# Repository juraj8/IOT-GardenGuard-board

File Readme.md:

# Garden Guard

GardenGuard is an IOT type device created for collecting temperature data from multiple points in our garden. Main usecase for this data is to give alert for freezing weather in spring months, so user can take mitigation steps to prevent frost of the blooming fruit trees.

Freezing in spring months takes a lot of fruits from our garden. This is an attempt to hopefully get more fruits of our garden.  

## Features

- Uses multiple DS18x20 sensors to sample surrounding temperature.
- Solar and battery powered. Battery is charged wia solar panel, if battery is full, device only runs out of solar.  
- Battery voltage measurement.
- Battery should last over span of whole winter

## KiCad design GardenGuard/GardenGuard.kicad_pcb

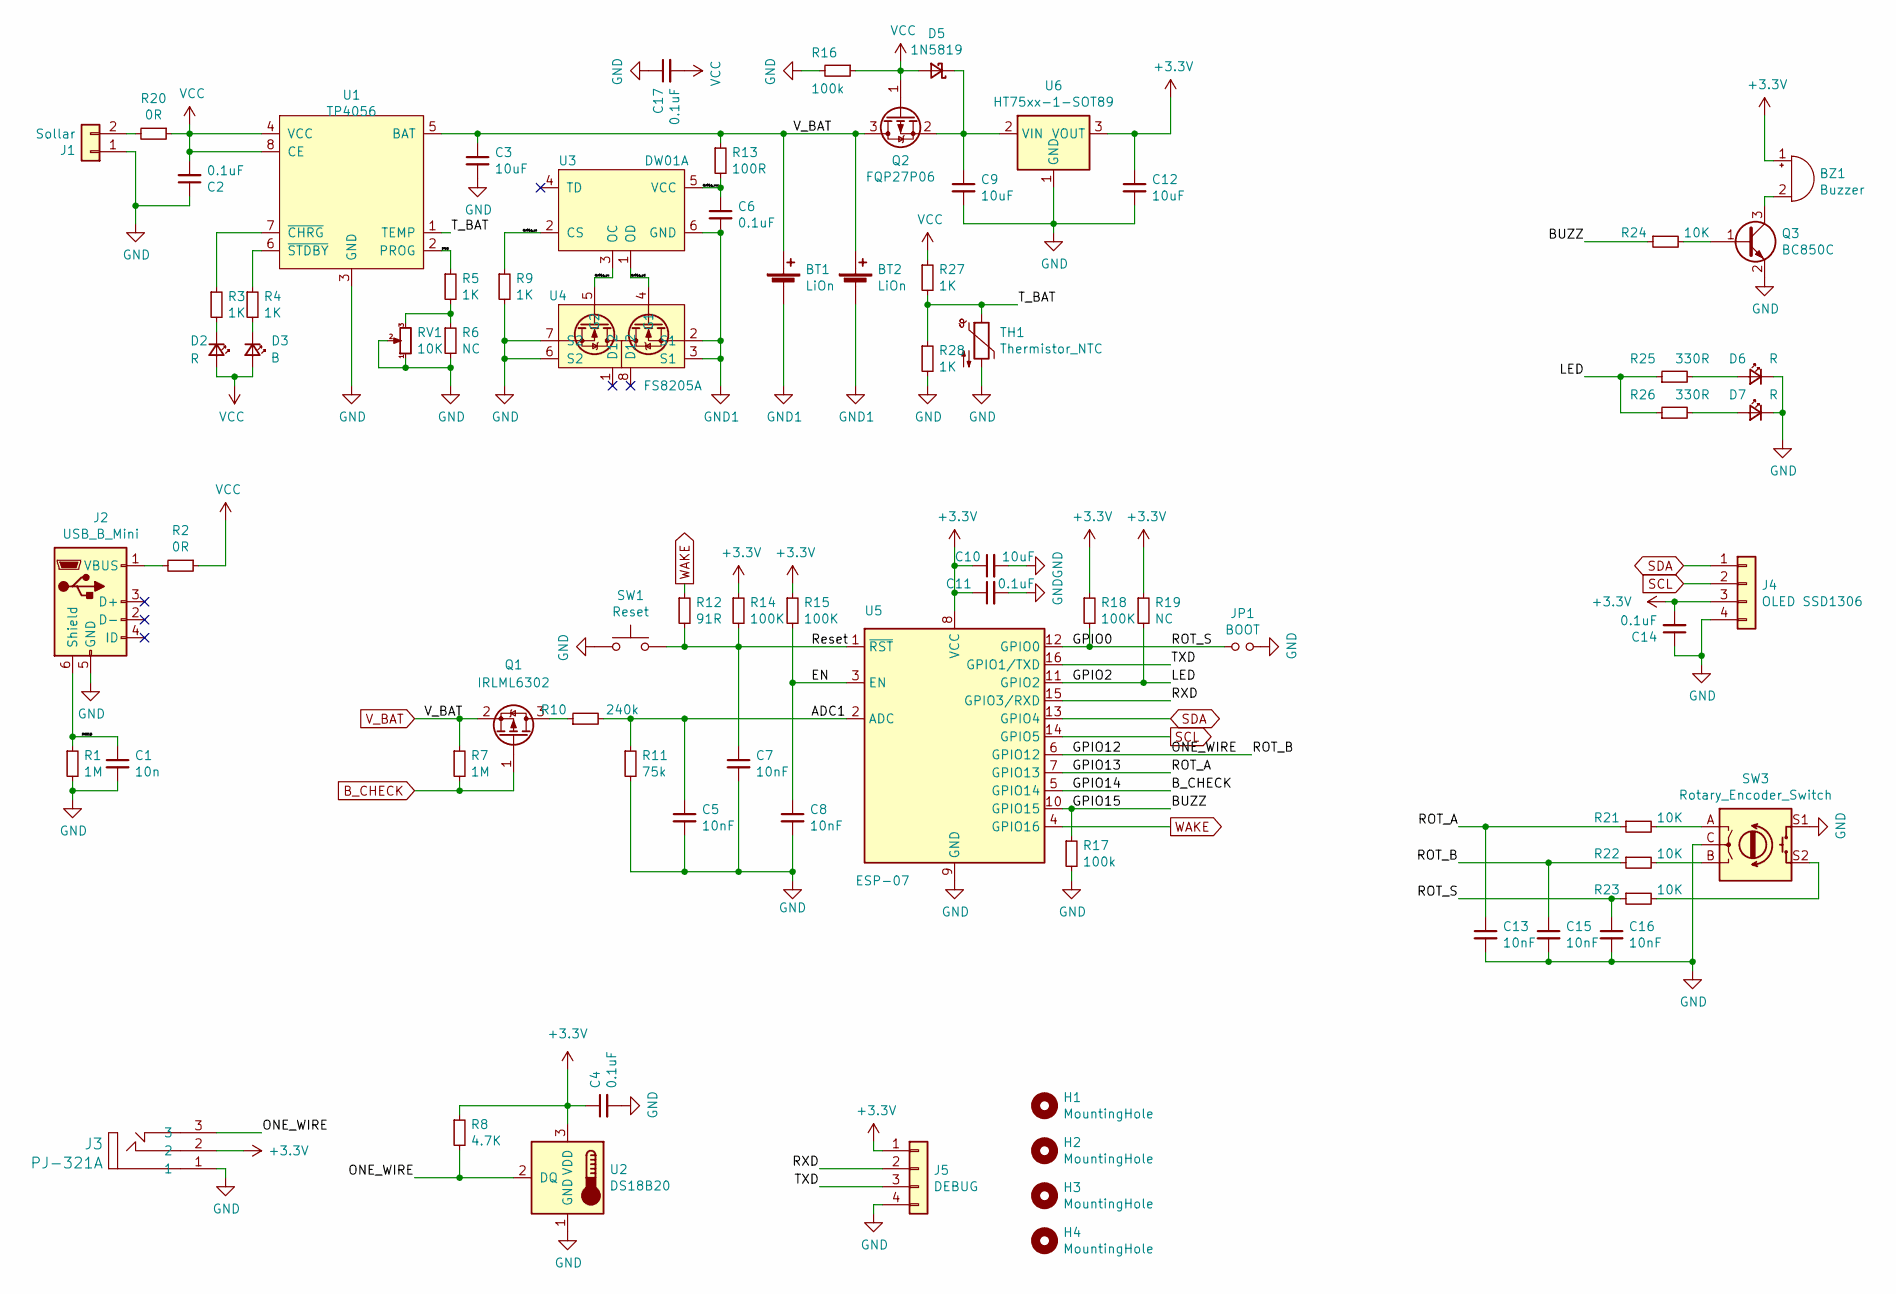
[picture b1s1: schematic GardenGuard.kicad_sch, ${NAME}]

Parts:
BT1, BT2: LiOn; BatteryHolder_Keystone_1042_1x18650
BZ1: Buzzer; Buzzer_12x9.5RM7.6
C1: 10n; C_0805_2012Metric_Pad1.18x1.45mm_HandSolder
C2, C17: 0.1uF; C_1206_3216Metric_Pad1.33x1.80mm_HandSolder
C3, C10: 10uF; C_1206_3216Metric_Pad1.33x1.80mm_HandSolder
C4, C6, C11, C14: 0.1uF; C_0805_2012Metric_Pad1.18x1.45mm_HandSolder
C5, C7, C8, C13, C15, C16: 10nF; C_0805_2012Metric_Pad1.18x1.45mm_HandSolder
C9, C12: 10uF; C_0805_2012Metric_Pad1.18x1.45mm_HandSolder
D2, D6, D7: R; LED_0805_2012Metric_Castellated
D3: B; LED_0805_2012Metric_Castellated
D5: 1N5819; D_SOD-123
H1, H2, H3, H4: MountingHole; MountingHole_3.2mm_M3_DIN965
J1: Sollar; ER-CON2.0-2P-SMD
J2: USB_B_Mini; USB_Micro-B_Amphenol_10118194_Horizontal
J3: PJ-321A
J4: OLED SSD1306; PinHeader_1x04_P2.54mm_Vertical
J5: DEBUG; PinHeader_1x04_P2.54mm_Vertical
JP1: BOOT; SolderJumper-2_P1.3mm_Open_RoundedPad1.0x1.5mm
Q1: IRLML6302; SOT-23_Handsoldering
Q2: FQP27P06; SOT-23_Handsoldering
Q3: BC850C; SOT-23_Handsoldering
R1, R7: 1M; R_0805_2012Metric_Pad1.20x1.40mm_HandSolder
R2, R20: 0R; R_0805_2012Metric_Pad1.20x1.40mm_HandSolder
R3, R4, R5, R9, R27, R28: 1K; R_0805_2012Metric_Pad1.20x1.40mm_HandSolder
R6, R19: NC; R_0805_2012Metric_Pad1.20x1.40mm_HandSolder
R8: 4.7K; R_0805_2012Metric_Pad1.20x1.40mm_HandSolder
R10: 240k; R_0805_2012Metric_Pad1.20x1.40mm_HandSolder
R11: 75k; R_0805_2012Metric_Pad1.20x1.40mm_HandSolder
R12: 91R; R_0805_2012Metric_Pad1.20x1.40mm_HandSolder
R13: 100R; R_0805_2012Metric_Pad1.20x1.40mm_HandSolder
R14, R15, R18: 100K; R_0805_2012Metric_Pad1.20x1.40mm_HandSolder
R16, R17: 100k; R_0805_2012Metric_Pad1.20x1.40mm_HandSolder
R21, R22, R23, R24: 10K; R_0805_2012Metric_Pad1.20x1.40mm_HandSolder
R25, R26: 330R; R_0805_2012Metric_Pad1.20x1.40mm_HandSolder
RV1: 10K; Potentiometer_Bourns_3224J_Horizontal
SW1: Reset; SW_SPST_B3U-3000P
SW3: Rotary_Encoder_Switch; RotaryEncoder_Alps_EC11E-Switch_Vertical_H20mm
TH1: Thermistor_NTC; R_Axial_DIN0204_L3.6mm_D1.6mm_P5.08mm_Horizontal
U1: TP4056; TP4056_SOP-8-PP
U2: DS18B20; TO-92_Inline
U3: DW01A; SOT-23-6
U4: FS8205A; TSSOP-8_4.4x3mm_P0.65mm
U5: ESP-07
U6: HT75xx-1-SOT89; SOT-89-3

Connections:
+3V3: BZ1.1 (-), C4.1, C10.1, C11.1, C12.1, C14.2, J3.2, J4.3, J5.1, R8.1, R14.1, R15.1, R18.1, R19.1, U2.3 (VDD), U5.8 (VCC), U6.3 (VOUT)
/ADC1: C5.1, R10.2, R11.1, U5.2 (ADC)
/BUZZ: R17.1, R24.1, U5.10 (GPIO15)
/EN: C8.1, R15.2, U5.3 (EN)
/GPIO0: C16.1, JP1.1, R18.2, R23.1, U5.12 (GPIO0)
/GPIO2: R19.2, R25.1, R26.1, U5.11 (GPIO2)
/GPIO12: C15.1, J3.3, R8.2, R22.1, U2.2 (DQ), U5.6 (GPIO12)
/GPIO13: C13.1, R21.1, U5.7 (GPIO13)
/RXD: J5.2, U5.15 (GPIO3/RXD)
/Reset: C7.1, R12.2, R14.2, SW1.2, U5.1 (~RST)
/SHIELD: C1.1, J2.6 (Shield), R1.1
/TXD: J5.3, U5.16 (GPIO1/TXD)
/T_BAT: R27.2, R28.1, TH1.1, U1.1 (TEMP)
/dw01a_cs: R9.1, U3.2 (CS)
/dw01a_oc: U3.3 (OC), U4.5 (G2)
/dw01a_od: U3.1 (OD), U4.4 (G1)
/dw01a_vcc: C6.1, R13.2, U3.5 (VCC)
/prog: R5.1, U1.2 (PROG)
B_CHECK: Q1.1 (G), R7.2, U5.5 (GPIO14)
GND: C1.2, C2.1, C3.2, C4.2, C5.2, C7.2, C8.2, C9.2, C10.2, C11.2, C12.2, C13.2, C14.1, C15.2, C16.2, C17.1, D6.1 (K), D7.1 (K), J1.1, J2.5 (GND), J3.1, J4.4, J5.4, JP1.2, Q3.2 (E), R1.2, R6.2, R9.2, R11.2, R16.2, R17.2, R28.2, RV1.1, RV1.2, SW1.1, SW3.C, SW3.S1, TH1.2, U1.3 (GND), U2.1 (GND), U4.6 (S2), U4.7 (S2), U5.9 (GND), U6.1 (GND)
GND1: BT1.2 (-), BT2.2 (-), C6.2, U3.6 (GND), U4.2 (S1), U4.3 (S1)
unnamed: BZ1.2 (+), Q3.3 (C)
unnamed: C9.1, D5.1 (K), Q2.2 (S), U6.2 (VIN)
unnamed: D2.1 (K), R3.2
unnamed: D3.1 (K), R4.2
unnamed: D6.2 (A), R25.2
unnamed: D7.2 (A), R26.2
unnamed: J1.2, R20.2
unnamed: J2.1 (VBUS), R2.2
unnamed: Q3.1 (B), R24.2
unnamed: R3.1, U1.7 (~CHRG)
unnamed: R4.1, U1.6 (~STDBY)
unnamed: R5.2, R6.1, RV1.3
unnamed: Q1.3 (D), R10.1
unnamed: R21.2, SW3.A
unnamed: R22.2, SW3.B
unnamed: R23.2, SW3.S2
SCL: J4.2, U5.14 (GPIO5)
SDA: J4.1, U5.13 (GPIO4)
VCC: C2.2, C17.2, D2.2 (A), D3.2 (A), D5.2 (A), Q2.1 (G), R2.1, R16.1, R20.1, R27.1, U1.4 (VCC), U1.8 (CE)
V_BAT: BT1.1 (+), BT2.1 (+), C3.1, Q1.2 (S), Q2.3 (D), R7.1, R13.1, U1.5 (BAT)
WAKE: R12.1, U5.4 (GPIO16)

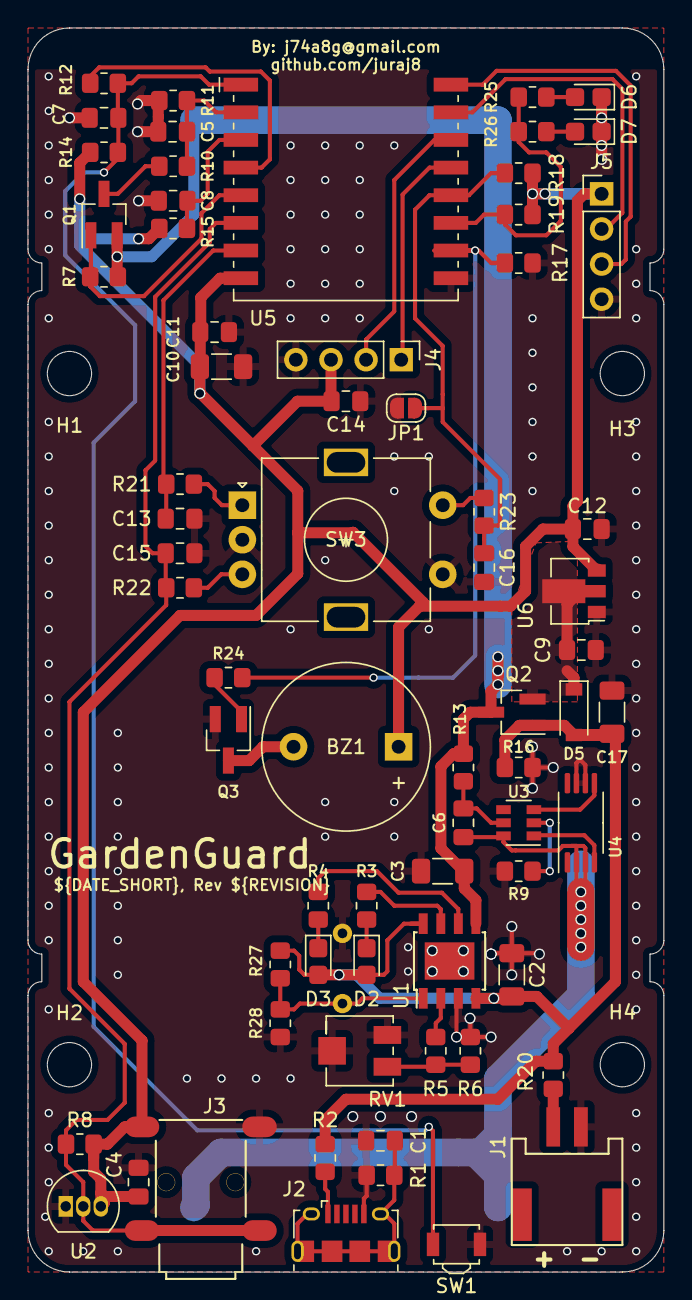
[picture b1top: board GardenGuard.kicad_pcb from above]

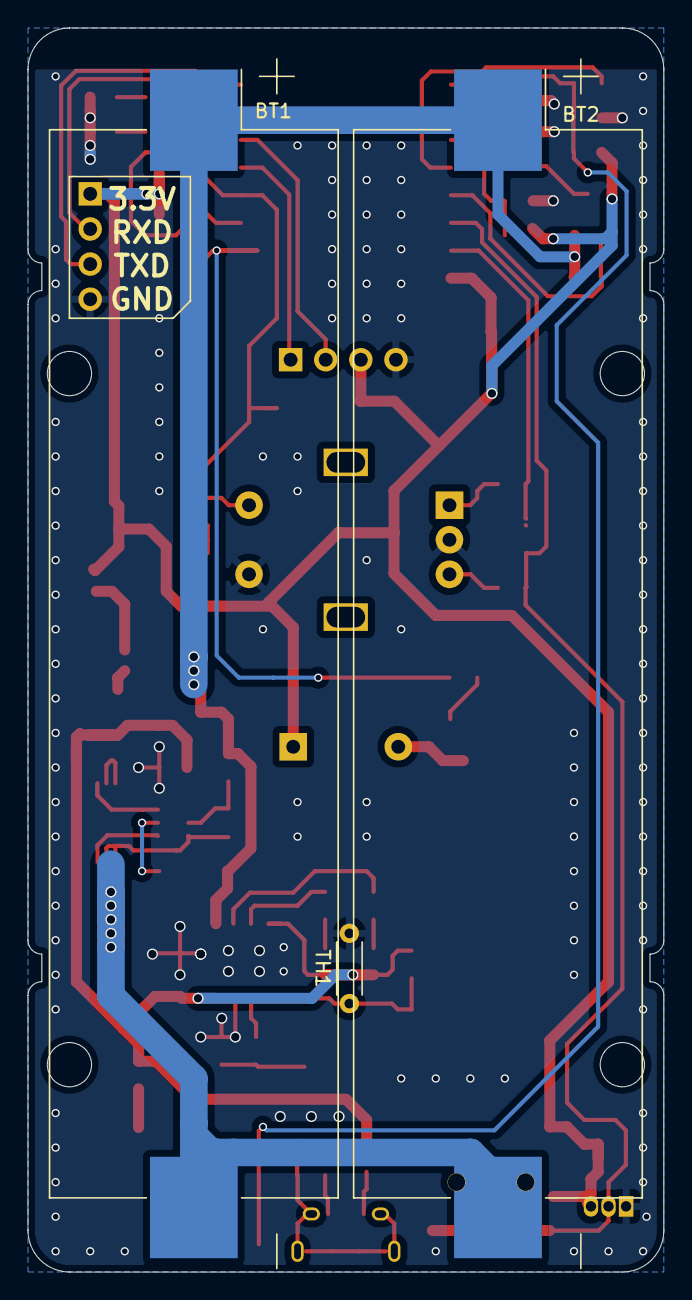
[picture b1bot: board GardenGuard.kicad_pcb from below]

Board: 2 copper layers, 46.0 x 90.0 mm, 76 parts (3 on the bottom side), 42 nets.

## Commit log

2021-05-09 Add empty KiCAD project files.
2021-05-09 Add programer schematic.
2021-07-19 Added powersupply stages
2021-07-21 shematic finished
2021-07-22 Updated packages, start layout
2021-07-24 layout done
2021-07-25 Release v1.0.0 - board finished
2022-01-15 Release v1.1.0 - update component values - cleanup
